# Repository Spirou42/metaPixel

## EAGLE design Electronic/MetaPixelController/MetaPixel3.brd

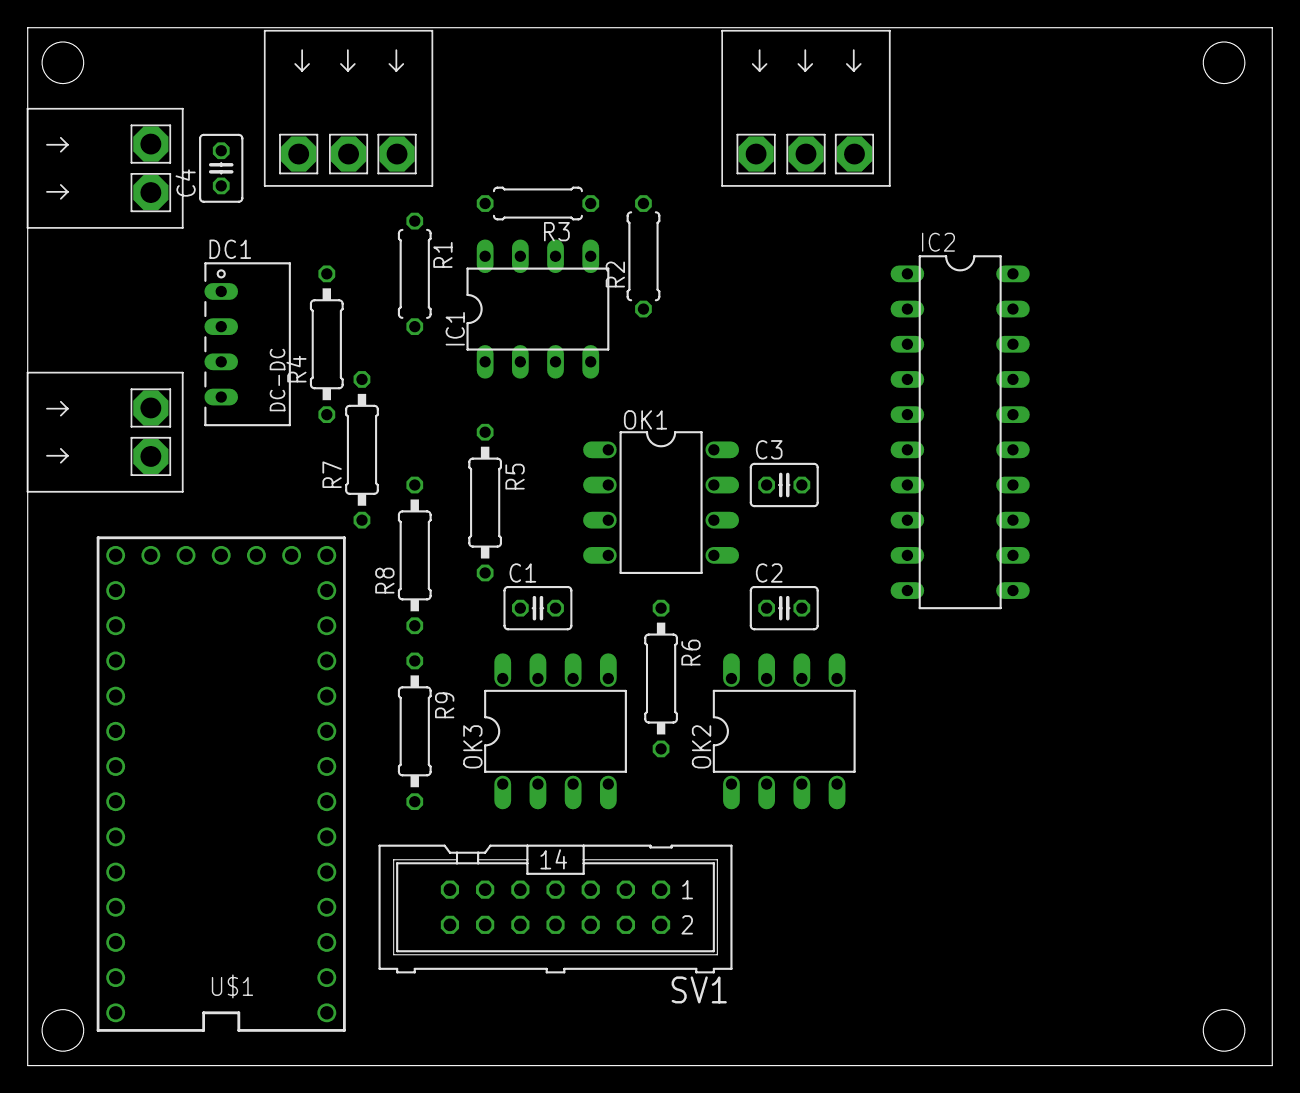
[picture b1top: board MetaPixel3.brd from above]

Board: 2 copper layers, 89.8 x 74.9 mm, 25 parts (0 on the bottom side), 29 nets, no tracks yet.

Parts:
C1, C2, C3, C4: 100n; C025-030X050
DC1: NME0505; NME
IC1: MAX481CPA; DIL08
IC2: 74HCT245N; DIL20
OK1, OK2, OK3: 6N137; DIL08
R1, R2: 562; 0207/7
R3: 133; 0207/7
R4, R8, R9: 470; 0207/10
R5, R6, R7: 4k7; 0207/10
SV1: UI-Port; ML14
U$1: TEENSY_3.0_BASIC
X1, X2: RIA_182_2
X3, X4: RIA_182_3

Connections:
3.3V: U$1.3.3V, U$1.3.3V1
+5V_EXT: C1.1, C2.1, C3.1, DC1.4, IC1.8, OK2.7, OK2.8, OK3.7, OK3.8, R1.2, R5.1, R6.1
DMX+: IC1.7, R1.1, R3.2, X3.1, X4.1
DMX-: IC1.6, R2.2, R3.1, X3.2, X4.2
DMX_DIR: IC2.13, R8.1
DMX_DIR3V: IC2.7, U$1.9
DMX_IN: OK1.6, R7.1, U$1.7
DMX_OUT: IC2.14, R9.1
DMX_OUT3V: IC2.6, U$1.8
ENC_DIR: SV1.11, U$1.4
ENC_PULSE: SV1.7, U$1.6
ENC_STEP: SV1.9, U$1.5
GND: C4.2, DC1.1, IC2.10, IC2.19, OK1.5, SV1.13, SV1.14, U$1.GND, U$1.GND1, X1.1
GND_EXT: C1.2, C2.2, C3.2, DC1.3, IC1.5, OK1.3, OK2.5, OK3.5, R2.1, X3.3, X4.3
LCD_CLK: IC2.16, SV1.12
LCD_CLK3V: IC2.4, U$1.2
LCD_CS: IC2.17, SV1.10
LCD_CS3V: IC2.3, U$1.1
LCD_DATA: IC2.15, SV1.8
LCD_DATA3V: IC2.5, U$1.3
LED_OUT: IC2.18, X2.2
LED_OUT3V: IC2.2, U$1.0
unnamed: OK1.2, R4.1
unnamed: IC1.1, R4.2
unnamed: IC1.2, IC1.3, OK2.6, R5.2
unnamed: IC1.4, OK3.6, R6.2
unnamed: OK3.3, R9.2
unnamed: OK2.3, R8.2
VCC: C4.1, DC1.2, IC2.1, IC2.20, OK1.7, OK1.8, OK2.2, OK3.2, R7.2, SV1.1, SV1.2, U$1.VIN, X1.2

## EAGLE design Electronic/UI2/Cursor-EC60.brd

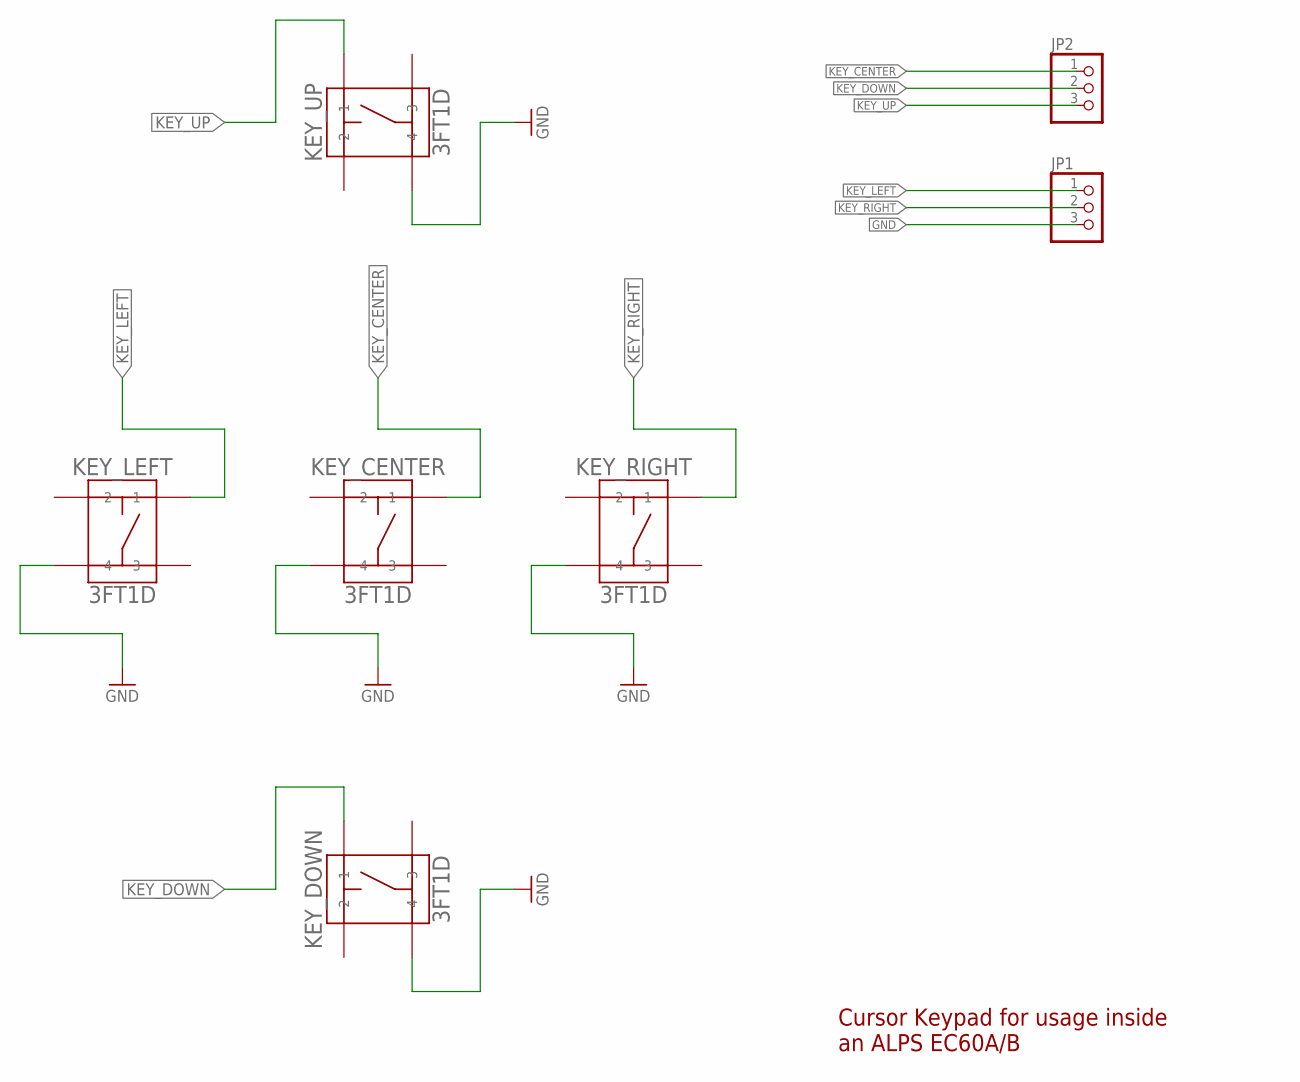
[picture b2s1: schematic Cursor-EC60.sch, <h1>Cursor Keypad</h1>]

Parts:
JP1, JP2: PINHD-1X3; 1X03
KEY_CENTER: 3FT1D; 3FT
KEY_DOWN: 3FT1D; 3FT
KEY_LEFT: 3FT1D; 3FT
KEY_RIGHT: 3FT1D; 3FT
KEY_UP: 3FT1D; 3FT

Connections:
GND: JP1.3, KEY_CENTER.P$4 (4), KEY_DOWN.P$4 (4), KEY_LEFT.P$4 (4), KEY_RIGHT.P$4 (4), KEY_UP.P$4 (4)
KEY_CENTER: JP2.1, KEY_CENTER.P$1 (1)
KEY_DOWN: JP2.2, KEY_DOWN.P$1 (1)
KEY_LEFT: JP1.1, KEY_LEFT.P$1 (1)
KEY_RIGHT: JP1.2, KEY_RIGHT.P$1 (1)
KEY_UP: JP2.3, KEY_UP.P$1 (1)

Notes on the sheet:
Cursor Keypad for usage inside an ALPS EC60A/B

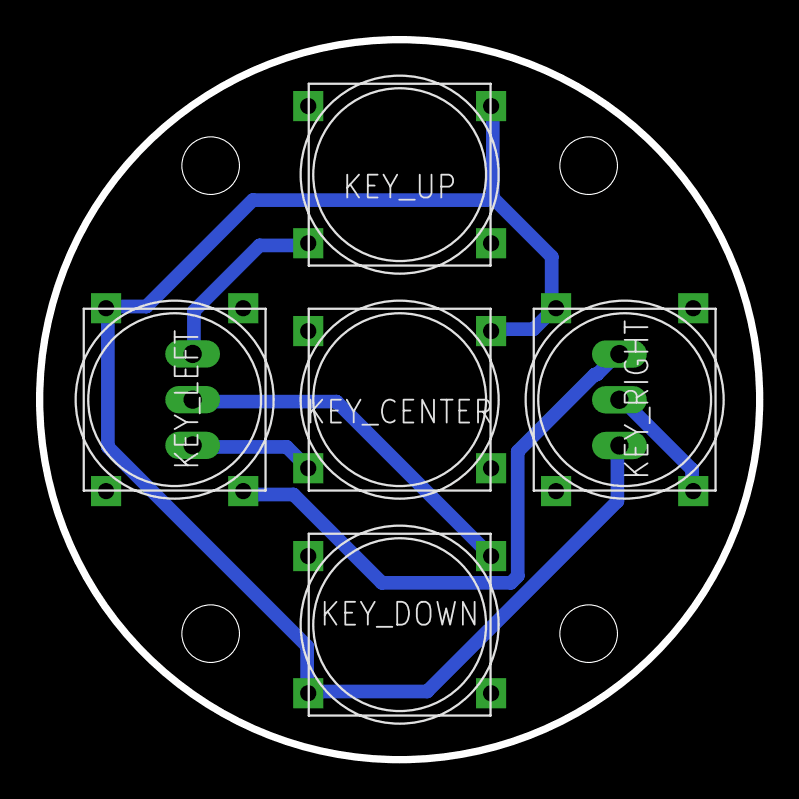
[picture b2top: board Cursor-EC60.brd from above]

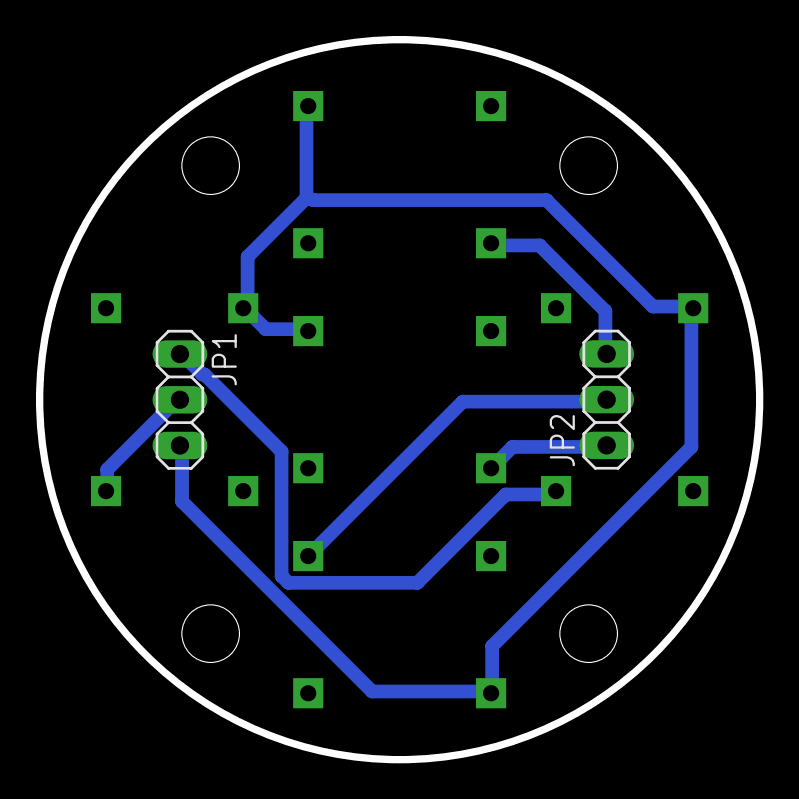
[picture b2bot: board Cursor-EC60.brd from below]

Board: 2 copper layers, 40.0 x 40.0 mm, 7 parts (2 on the bottom side), 6 nets.

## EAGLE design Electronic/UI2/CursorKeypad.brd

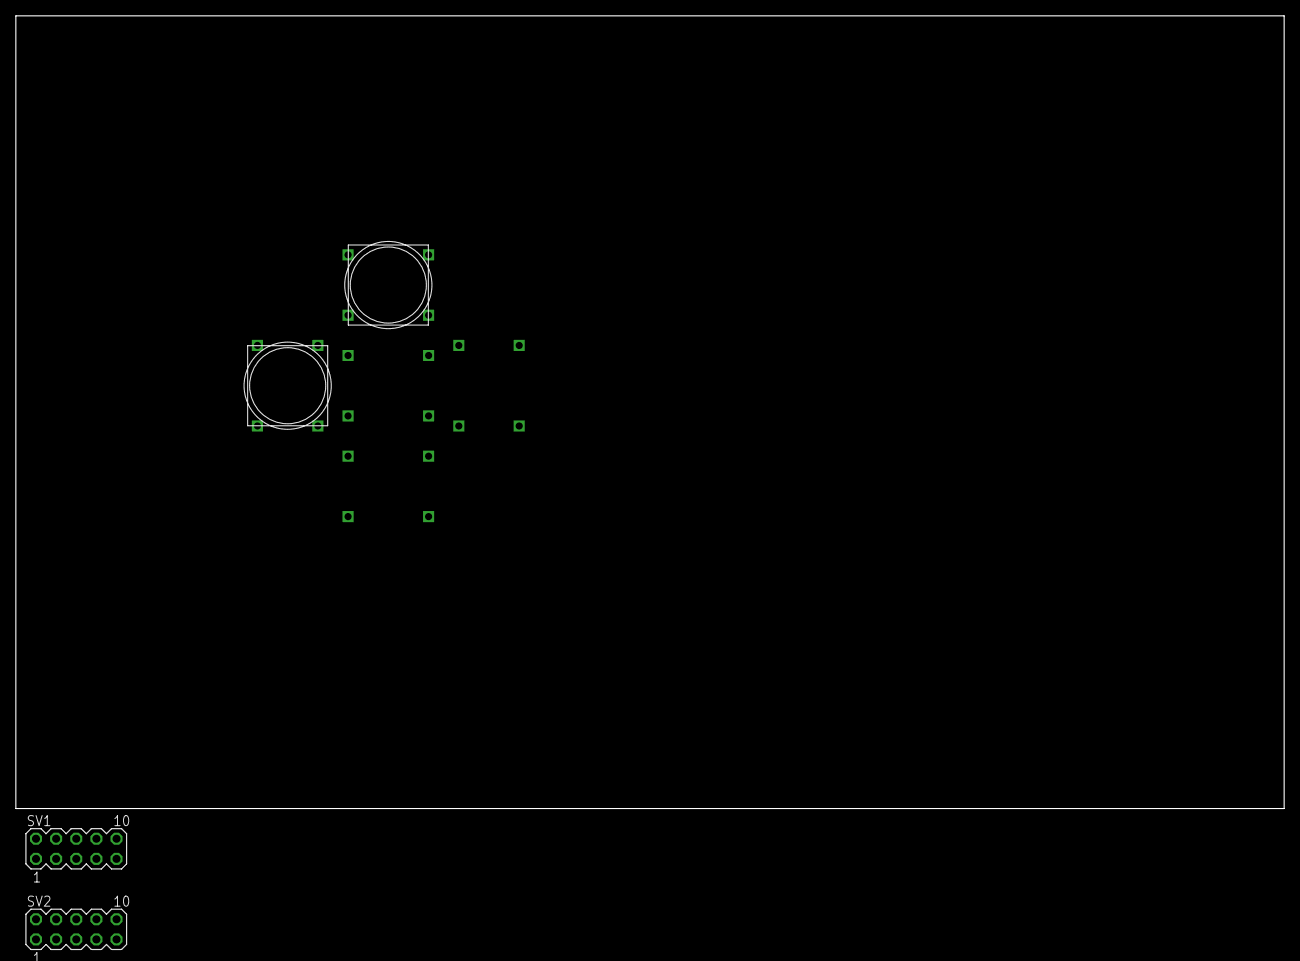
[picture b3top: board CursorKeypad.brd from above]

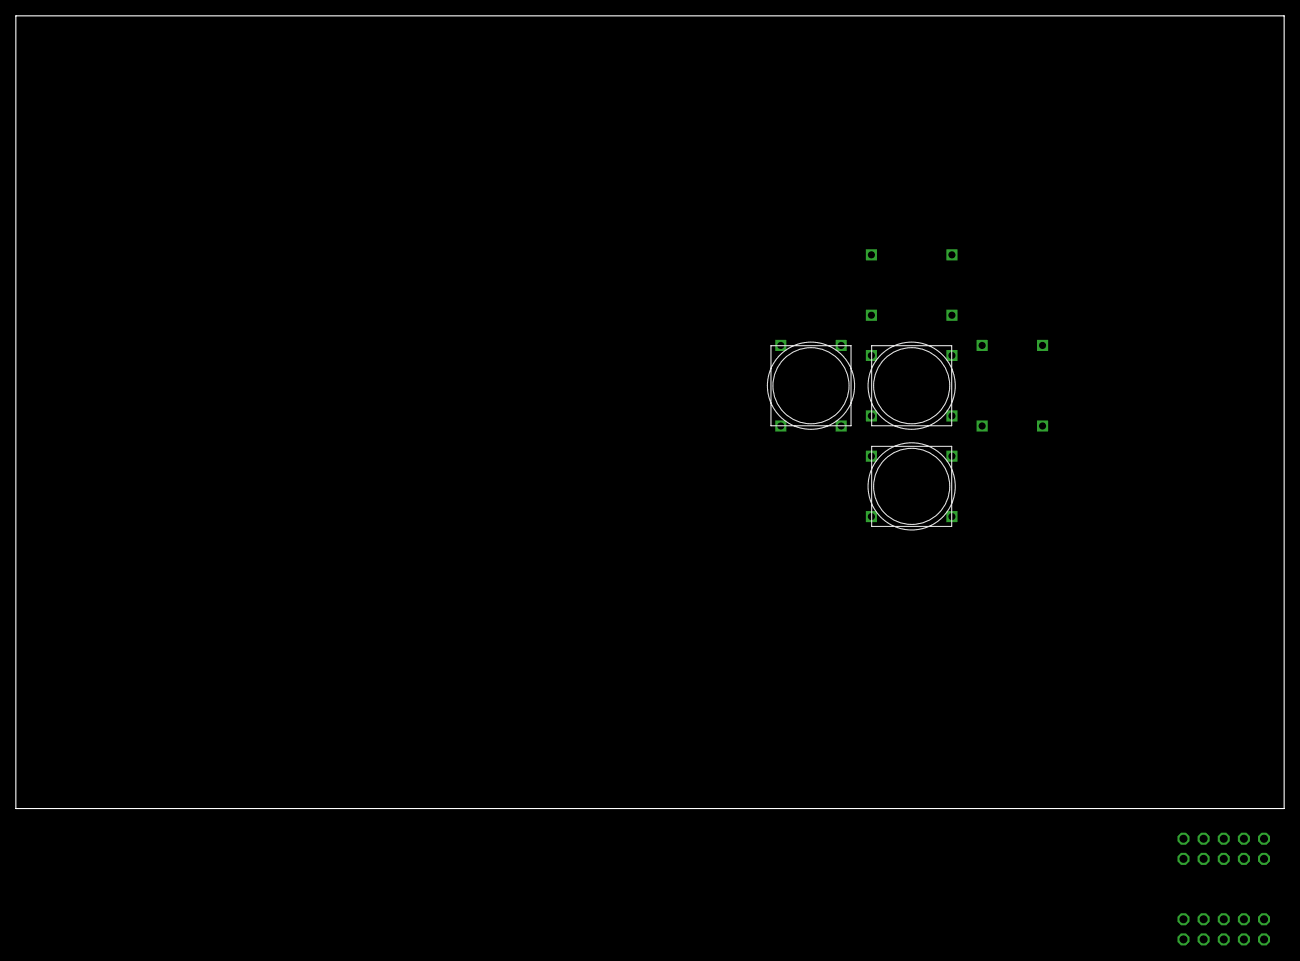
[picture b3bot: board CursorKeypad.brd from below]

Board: 2 copper layers, 160.0 x 100.0 mm, 7 parts (3 on the bottom side), 10 nets, no tracks yet.

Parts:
KEY_CENTER: 3FT1D; 3FT
KEY_DOWN: 3FT1D; 3FT
KEY_LEFT: 3FT1D; 3FT
KEY_RIGHT: 3FT1D; 3FT
KEY_UP: 3FT1D; 3FT
SV1: Debounce L; MA05-2
SV2: Debounce R; MA05-2

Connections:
GND: KEY_CENTER.P$3, KEY_CENTER.P$4, KEY_DOWN.P$3, KEY_DOWN.P$4, KEY_LEFT.P$3, KEY_LEFT.P$4, KEY_RIGHT.P$3, KEY_RIGHT.P$4, KEY_UP.P$3, KEY_UP.P$4, SV2.1, SV2.2
KEY_CENTER: KEY_CENTER.P$1, KEY_CENTER.P$2, SV1.9, SV1.10
KEY_DOWN: KEY_DOWN.P$1, KEY_DOWN.P$2, SV1.7, SV1.8
KEY_LEFT: KEY_LEFT.P$1, KEY_LEFT.P$2, SV1.3, SV1.4
KEY_RIGHT: KEY_RIGHT.P$1, KEY_RIGHT.P$2, SV1.1, SV1.2
KEY_UP: KEY_UP.P$1, KEY_UP.P$2, SV1.5, SV1.6
unnamed: SV2.9, SV2.10
unnamed: SV2.7, SV2.8
unnamed: SV2.5, SV2.6
unnamed: SV2.3, SV2.4

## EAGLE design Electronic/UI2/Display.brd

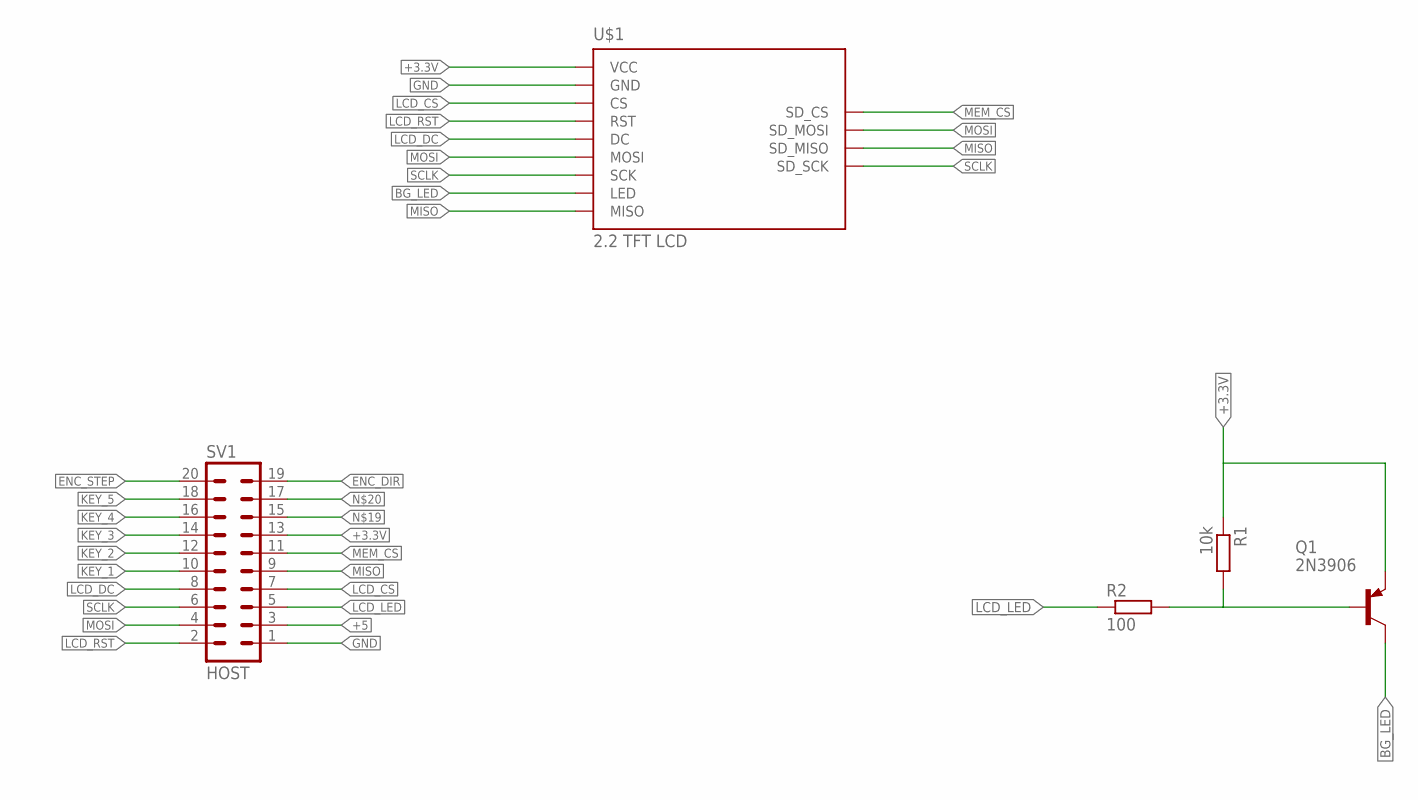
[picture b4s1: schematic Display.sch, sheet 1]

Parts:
Q1: 2N3906; TO92
R1: 10k; 0204/7
R2: 100; 0204/7
SV1: HOST; ML20L
U$1: 2.2_TFT_LCD

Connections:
!LCD_CS: SV1.7, U$1.CS
!LCD_RST: SV1.2, U$1.RST
!MEM_CS: SV1.11, U$1.SD_CS
+3.3V: Q1.3 (E), R1.1, SV1.13, U$1.VCC; also elsewhere on the board
+5: SV1.3
BG_LED: Q1.1 (C), U$1.LED
ENC_DIR: SV1.19; also elsewhere on the board
ENC_STEP: SV1.20; also elsewhere on the board
GND: SV1.1, U$1.GND; also elsewhere on the board
KEY_1: SV1.10; also elsewhere on the board
KEY_2: SV1.12; also elsewhere on the board
KEY_3: SV1.14; also elsewhere on the board
KEY_4: SV1.16; also elsewhere on the board
KEY_5: SV1.18; also elsewhere on the board
LCD_DC: SV1.8, U$1.DC
LCD_LED: R2.1, SV1.5
MISO: SV1.9, U$1.MISO, U$1.SD_MISO
MOSI: SV1.4, U$1.MOSI, U$1.SD_MOSI
unnamed: Q1.2 (B), R1.2, R2.2
SCLK: SV1.6, U$1.SCK, U$1.SD_SCK

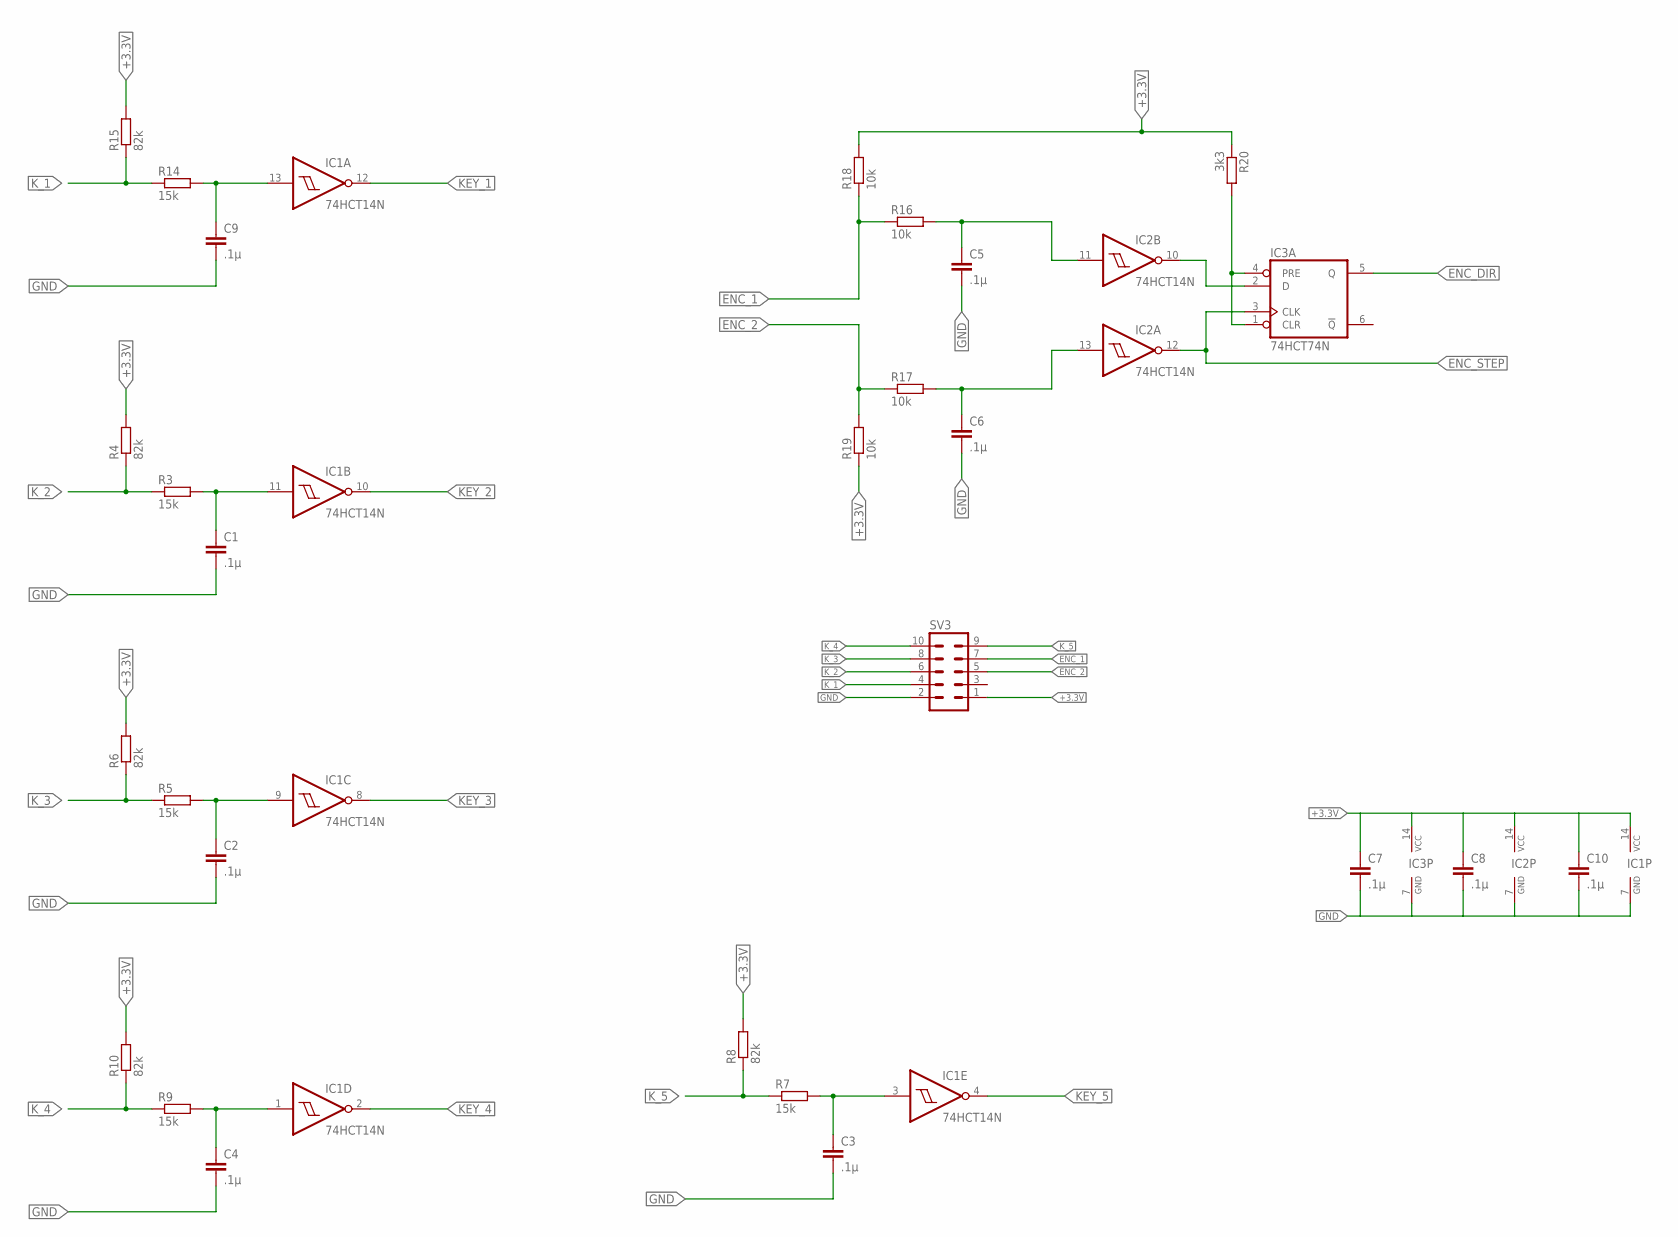
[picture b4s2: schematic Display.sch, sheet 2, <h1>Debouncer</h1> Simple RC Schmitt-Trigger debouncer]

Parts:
C1, C2, C3, C4, C5, C6, C7, C8, C9, C10: .1µ; C025-024X044
IC1, IC2: 74HCT14N; DIL14
IC3: 74HCT74N; DIL14
R3, R5, R7, R9, R14: 15k; 0204/7
R4, R6, R8, R10, R15: 82k; 0204/7
R16, R17, R18, R19: 10k; 0204/7
R20: 3k3; 0204/7
SV3: ML10L

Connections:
+3.3V: C7.1, C8.1, C10.1, IC1.14 (VCC), IC2.14 (VCC), IC3.14 (VCC), R4.2, R6.2, R8.2, R10.2, R15.2, R18.2, R19.1, R20.1, SV3.1; also elsewhere on the board
ENC1: C5.1, IC2.11 (I), R16.2
ENC2: C6.1, IC2.13 (I), R17.2
ENC_1: R16.1, R18.1, SV3.7
ENC_2: R17.1, R19.2, SV3.5
ENC_DIR: IC3.5 (Q); also elsewhere on the board
ENC_STEP: IC2.12 (O), IC3.3 (CLK); also elsewhere on the board
GND: C1.2, C2.2, C3.2, C4.2, C5.2, C6.2, C7.2, C8.2, C9.2, C10.2, IC1.7 (GND), IC2.7 (GND), IC3.7 (GND), SV3.2; also elsewhere on the board
K1: C9.1, IC1.13 (I), R14.2
K2: C1.1, IC1.11 (I), R3.2
K3: C2.1, IC1.9 (I), R5.2
K4: C3.1, IC1.3 (I), R7.2
K5: C4.1, IC1.1 (I), R9.2
KEY_1: IC1.12 (O); also elsewhere on the board
KEY_2: IC1.10 (O); also elsewhere on the board
KEY_3: IC1.8 (O); also elsewhere on the board
KEY_4: IC1.2 (O); also elsewhere on the board
KEY_5: IC1.4 (O); also elsewhere on the board
K_1: R14.1, R15.1, SV3.4
K_2: R3.1, R4.1, SV3.6
K_3: R5.1, R6.1, SV3.8
K_4: R9.1, R10.1, SV3.10
K_5: R7.1, R8.1, SV3.9
unnamed: IC2.10 (O), IC3.2 (D)
unnamed: IC3.1 (CLR), IC3.4 (PRE), R20.2

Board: 2 copper layers, 34 parts (1 on the bottom side), 35 nets, no tracks yet.

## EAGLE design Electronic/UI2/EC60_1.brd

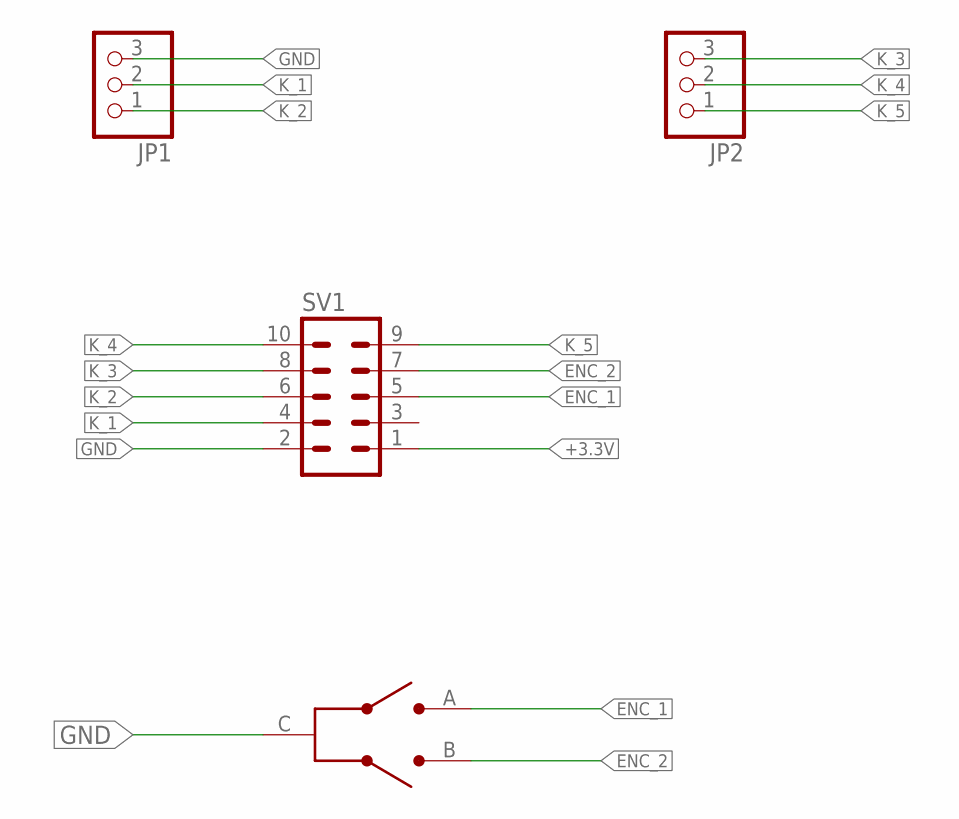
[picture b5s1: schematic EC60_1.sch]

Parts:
JP1, JP2: PINHD-1X3; 1X03
SV1: ML10L
U$1: EC60A

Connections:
+3.3V: SV1.1
ENC_1: SV1.5, U$1.A
ENC_2: SV1.7, U$1.B
GND: JP1.3, SV1.2, U$1.C
K_1: JP1.2, SV1.4
K_2: JP1.1, SV1.6
K_3: JP2.3, SV1.8
K_4: JP2.2, SV1.10
K_5: JP2.1, SV1.9

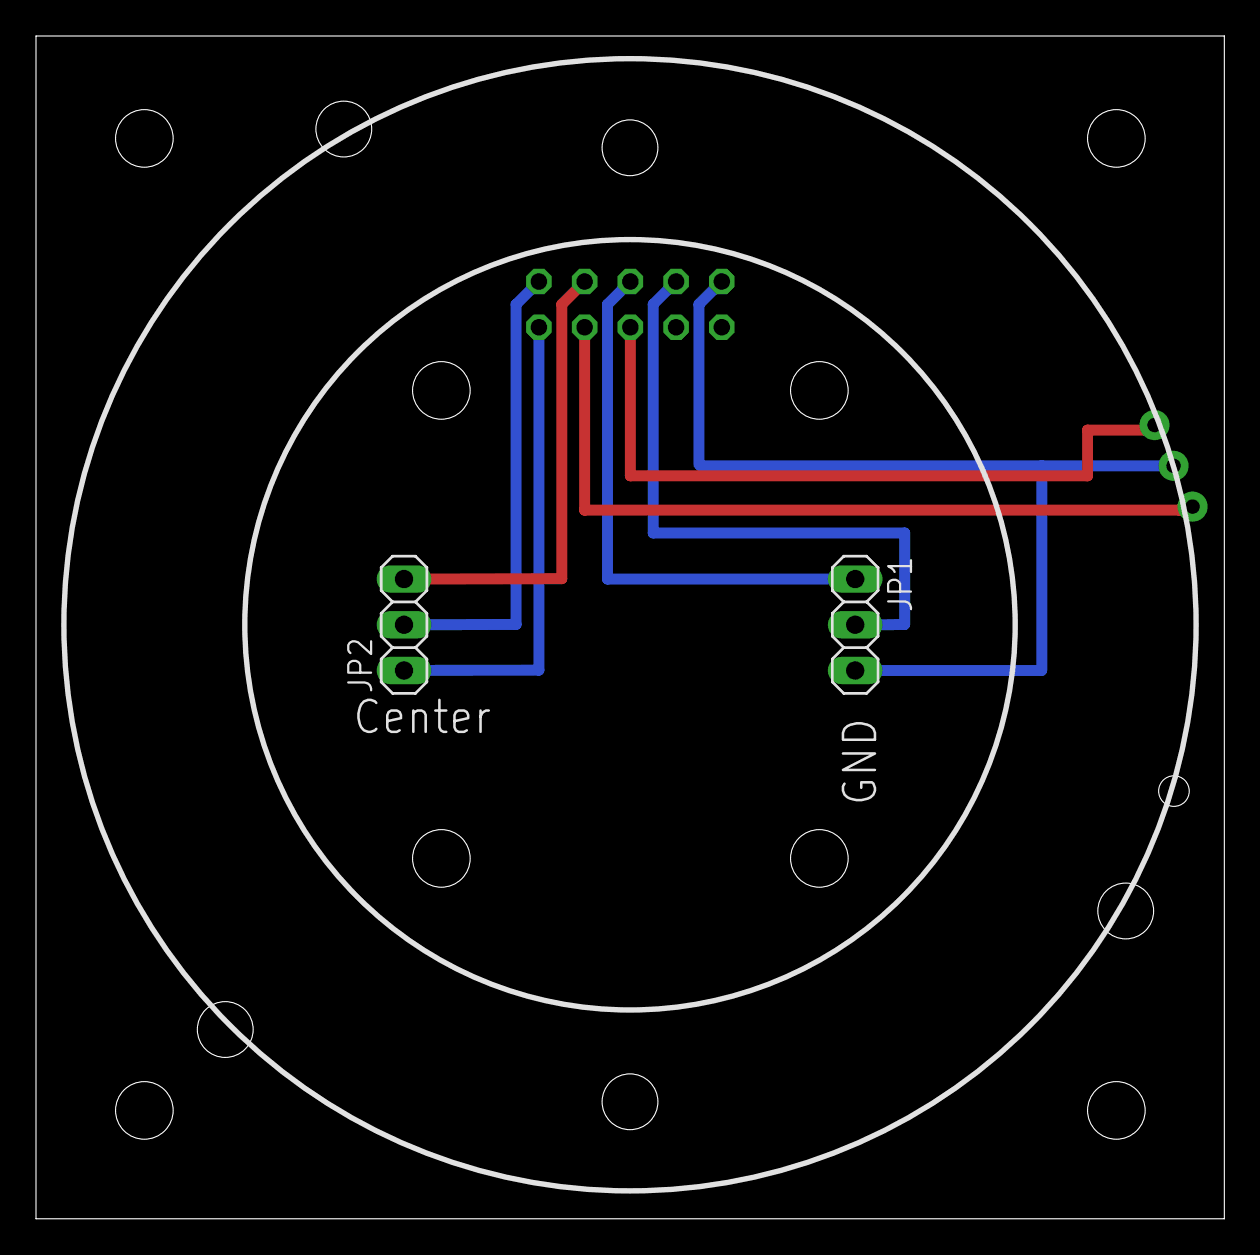
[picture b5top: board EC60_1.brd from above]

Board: 2 copper layers, 66.0 x 65.7 mm, 4 parts (1 on the bottom side), 8 nets.

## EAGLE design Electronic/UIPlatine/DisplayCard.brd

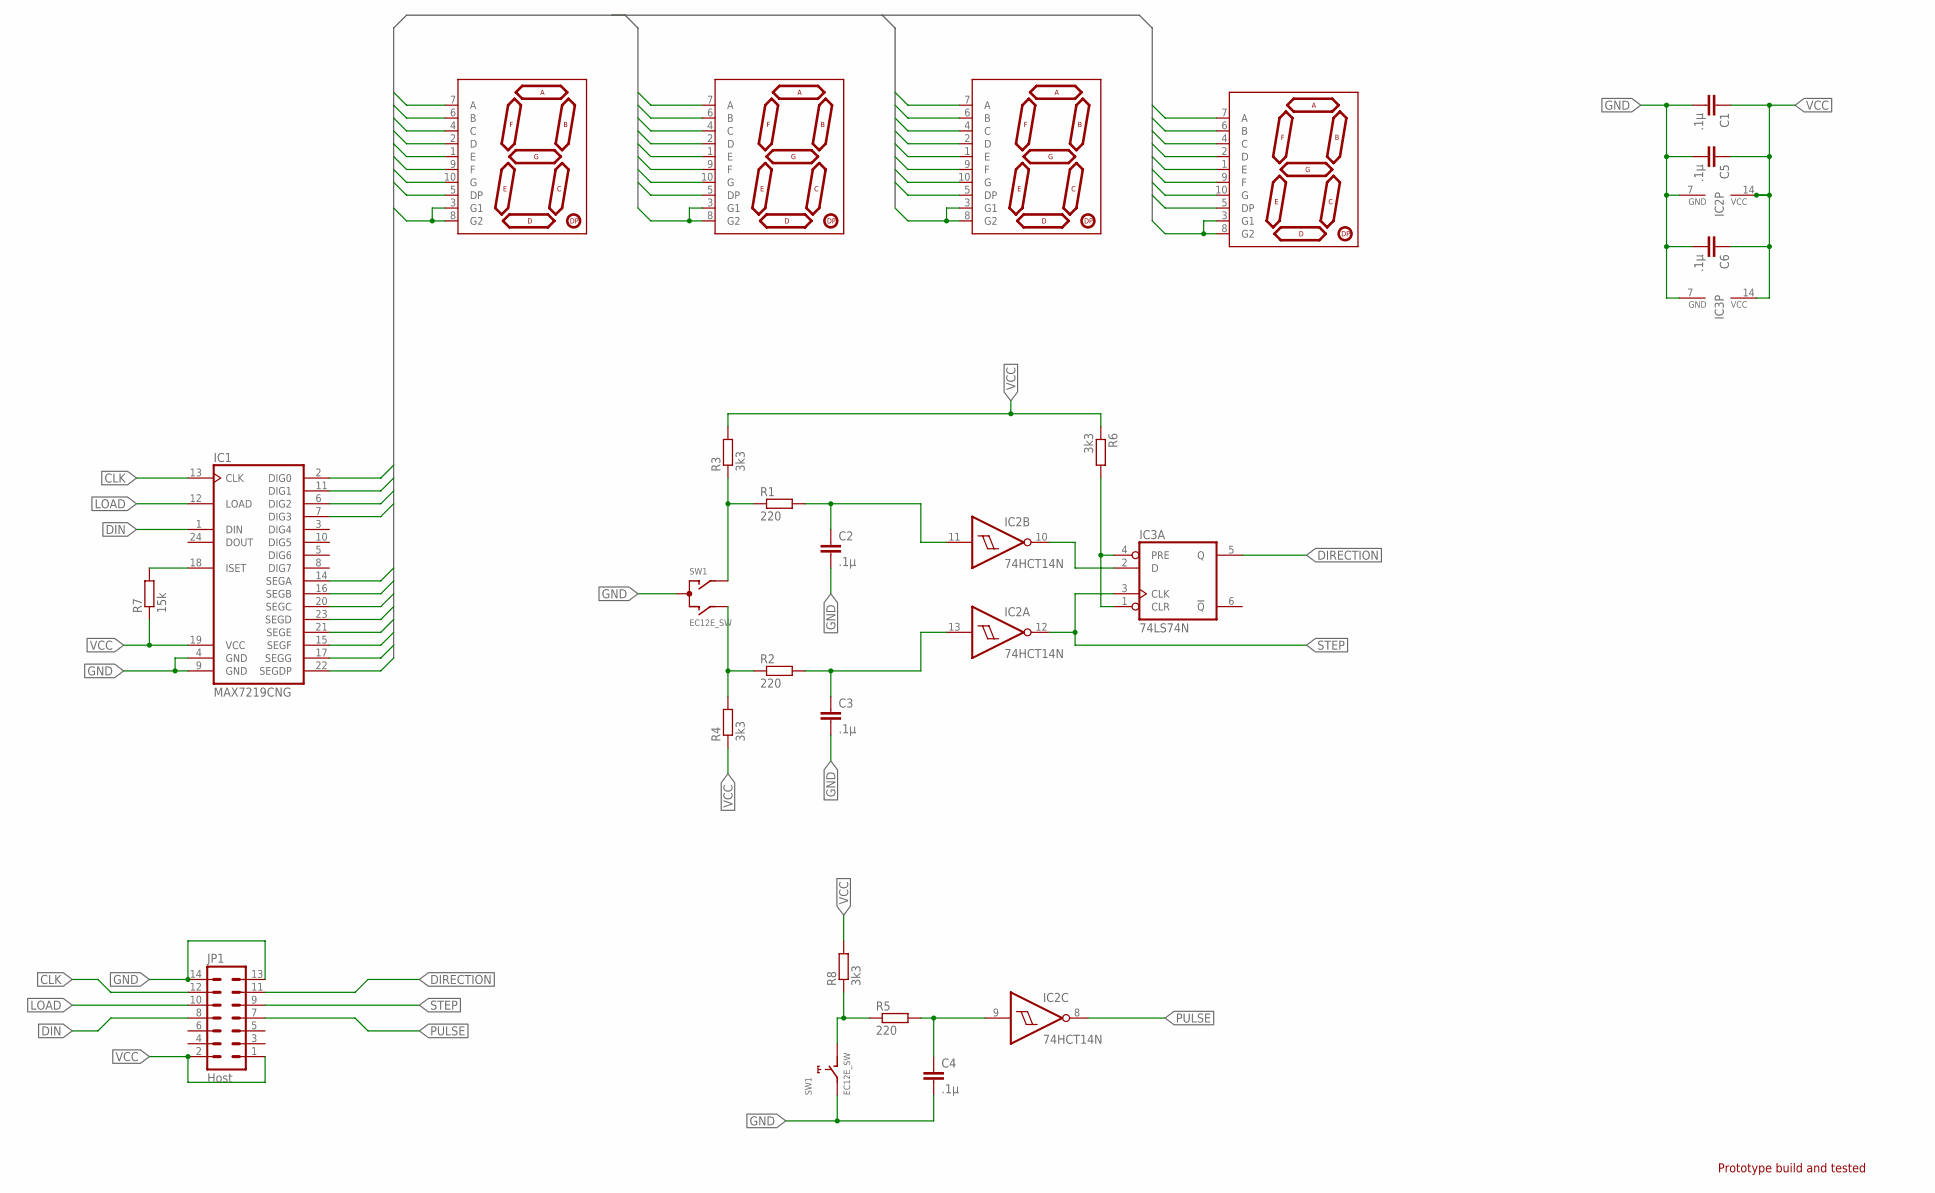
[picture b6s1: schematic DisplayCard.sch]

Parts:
C1, C2, C3, C4, C5, C6: .1µ; C025-024X044
DIGI4: 7-SEGMENT-DISPLAYPTH; 7-SEGMENT-DISPLAY
DIGIT1, DIGIT2, DIGIT3: 7-SEGMENT-DISPLAYPTH; 7-SEGMENT-DISPLAY
IC1: MAX7219CNG; DIL24-3
IC2: 74HCT14N; DIL14
IC3: 74LS74N; DIL14
JP1: Host; ML14L
R1, R2, R5: 220; 0204/7
R3, R4, R6, R8: 3k3; 0204/7
R7: 15k; 0204/7
SW1: EC12E_SW; ALPS_EC12E_SW

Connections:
A: DIGI4.7 (A), DIGIT1.7 (A), DIGIT2.7 (A), DIGIT3.7 (A), IC1.14 (SEGA)
B: DIGI4.6 (B), DIGIT1.6 (B), DIGIT2.6 (B), DIGIT3.6 (B), IC1.16 (SEGB)
C: DIGI4.4 (C), DIGIT1.4 (C), DIGIT2.4 (C), DIGIT3.4 (C), IC1.20 (SEGC)
CLK: IC1.13 (CLK), JP1.12
D: DIGI4.2 (D), DIGIT1.2 (D), DIGIT2.2 (D), DIGIT3.2 (D), IC1.23 (SEGD)
D0: DIGIT1.3 (G1), DIGIT1.8 (G2), IC1.2 (DIG0)
D1: DIGIT2.3 (G1), DIGIT2.8 (G2), IC1.11 (DIG1)
D2: DIGIT3.3 (G1), DIGIT3.8 (G2), IC1.6 (DIG2)
D3: DIGI4.3 (G1), DIGI4.8 (G2), IC1.7 (DIG3)
DIN: IC1.1 (DIN), JP1.8
DIRECTION: IC3.5 (Q), JP1.11
DP: DIGI4.5 (DP), DIGIT1.5 (DP), DIGIT2.5 (DP), IC1.22 (SEGDP)
E: DIGI4.1 (E), DIGIT1.1 (E), DIGIT2.1 (E), DIGIT3.1 (E), IC1.21 (SEGE)
ENC1: C2.1, IC2.11 (I), R1.2
ENC2: C3.1, IC2.13 (I), R2.2
F: DIGI4.9 (F), DIGIT1.9 (F), DIGIT2.9 (F), DIGIT3.9 (F), IC1.15 (SEGF)
G: DIGI4.10 (G), DIGIT1.10 (G), DIGIT2.10 (G), DIGIT3.5 (DP), DIGIT3.10 (G), IC1.17 (SEGG)
GND: C1.2, C2.2, C3.2, C4.2, C5.2, C6.2, IC1.4 (GND), IC1.9 (GND), IC2.7 (GND), IC3.7 (GND), JP1.13, JP1.14, SW1.C, SW1.E (2)
K: C4.1, IC2.9 (I), R5.2
LOAD: IC1.12 (LOAD), JP1.10
unnamed: R1.1, R3.1, SW1.A
unnamed: IC3.1 (CLR), IC3.4 (PRE), R6.2
unnamed: R2.1, R4.2, SW1.B
unnamed: R5.1, R8.1, SW1.D (1)
unnamed: IC2.10 (O), IC3.2 (D)
unnamed: IC1.18 (ISET), R7.2
PULSE: IC2.8 (O), JP1.7
STEP: IC2.12 (O), IC3.3 (CLK), JP1.9
VCC: C1.1, C5.1, C6.1, IC1.19 (VCC), IC2.14 (VCC), IC3.14 (VCC), JP1.1, JP1.2, R3.2, R4.1, R6.1, R7.1, R8.2

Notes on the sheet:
Prototype build and tested

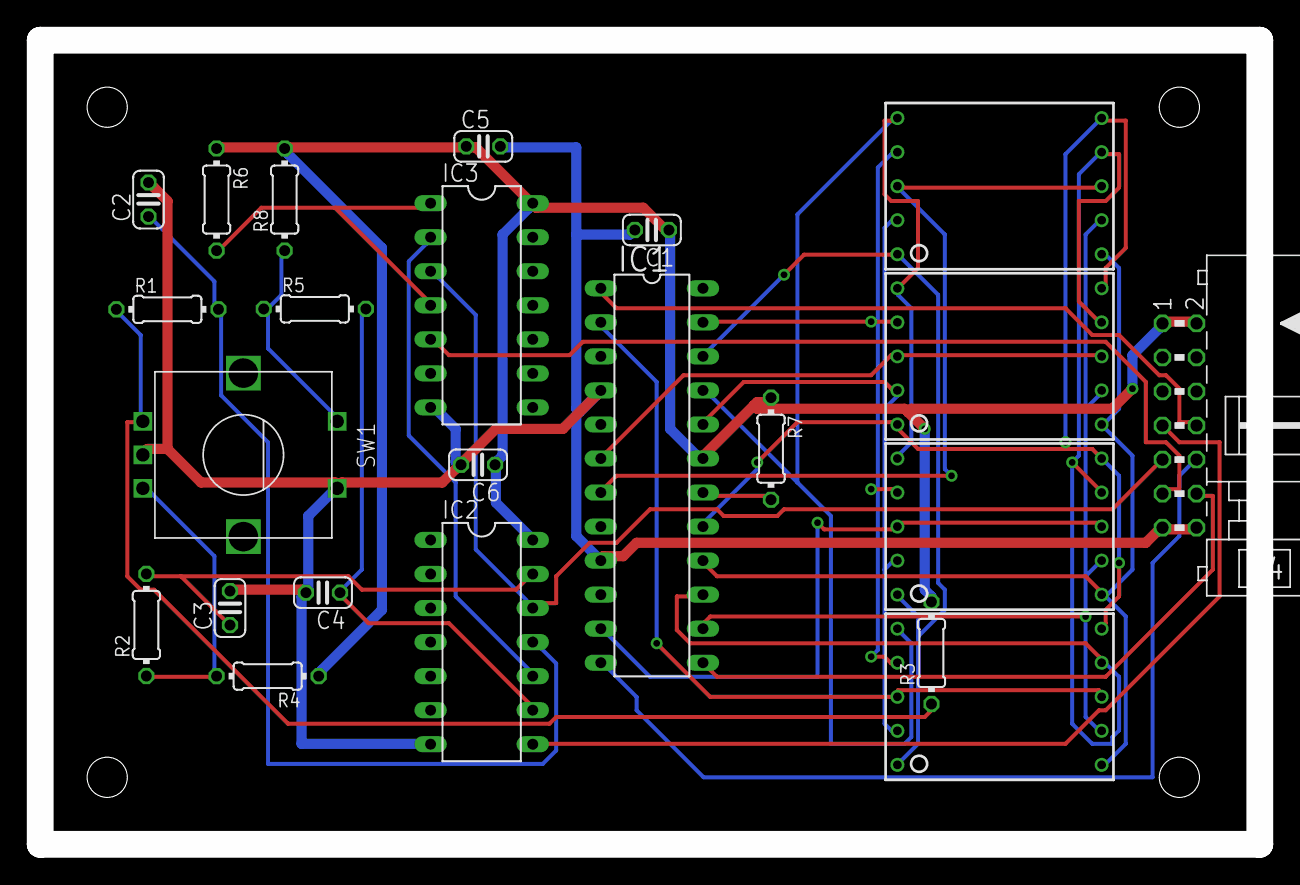
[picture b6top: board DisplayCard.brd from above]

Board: 2 copper layers, 91.0 x 60.0 mm, 23 parts (0 on the bottom side), 29 nets.
